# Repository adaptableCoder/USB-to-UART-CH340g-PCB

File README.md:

# USB to UART Converter (CH340G)

A compact **USB-to-UART adapter** based on the **CH340G**, implemented as a **USB-A edge connector board**.
Fabrication files have been generated; board fabrication is pending.

---

## Overview

This project implements a reliable USB-to-UART interface suitable for development, debugging, and embedded bring-up tasks.
Unlike typical breakout boards, this design uses a **USB-A edge connector**, allowing direct insertion into a host USB port without a cable.

The board supports both **5 V and 3.3 V UART logic levels** via jumper selection.

---

## Key Features

* CH340G USB-to-UART bridge
* USB-A **edge connector** (ENIG finish, bevelled)
* Jumper-selectable UART logic level (5 V / 3.3 V)
* On-board 3.3 V LDO
* USB ESD protection
* Polyfuse on VBUS for over-current protection
* Status LEDs (Power, TX, RX)
* RTS / CTS / DTR / DSR signals exposed
* 2-layer PCB, 1.6 mm thickness

---

## Design Tools Used

- KiCad (schematic capture, PCB layout, Gerber generation)

---

## Design Highlights

* **Grounding strategy**

  * Ground stitching vias near USB connector, ESD, and IC
  * Controlled return paths for high-speed signals

* **Clock integrity**

  * 12 MHz crystal placed close to XI/XO pins
  * Symmetric routing and tight loop area
  * Dedicated ground vias for crystal capacitors

* **Manufacturability**

  * ENIG finish selected for USB edge reliability
  * Bevelled edge specified for connector durability
  * Clean DRC-verified Gerber output

---

## Repository Structure

```
usb-to-uart-ch340g-pcb/
├── README.md
├── LICENSE
├── docs/
│   ├── images/
│   └── design-notes.md
├── schematic/
│   └── usb-to-uart-ch340g_schematic.pdf
├── pcb/
│   └── layout_screenshots/
├── fabrication/
│   ├── USB-to-UART-CH340G_Gerbers.zip
│   └── fab-notes.txt
├── datasheet/
│   └── CH340G_datasheet.pdf
└── KiCAD files/
    ├── usb-to-uart.kicad_pro
    ├── usb-to-uart.kicad_sch
    ├── usb-to-uart.kicad_prl
    └── usb-to-uart.kicad_pcb
```
---

## Fabrication Details

* Layers: 2
* Board thickness: 1.6 mm
* Copper weight: 1 oz
* Surface finish: ENIG
* USB edge connector: bevelled
* Solder mask: standard

---

## References and Attribution

* The USB-A edge connector footprint is **adapted from an open-source KiCad footprint library**. The original library is referenced here for attribution: https://github.com/vasya-zh/PCB-Edge-USB-connector-KiCad-library

* Component selection and implementation follow the **WCH CH340G datasheet** and standard USB Full-Speed design guidelines.

* Some YouTube tutorials and online articles on USB-to-UART designs were consulted during development.<br/>
[PCB Cupid](https://www.youtube.com/playlist?list=PLn6004q9oeqGl91KifK6xHGuqvXGb374G) <br/>
[Hardik Seth](https://www.youtube.com/@DIYwithHardik) <br/>
[Electronics Globe](https://www.youtube.com/@electronicsglobeofficial)

---

## License

This project is released under the **MIT License** unless stated otherwise.
Third-party references retain their respective licenses.

---

## Notes

This project was built as a **practical hardware design exercise**, with emphasis on finishing a complete, manufacturable PCB rather than producing a minimal demo board.
Future revisions may explore USB-C support or auto-voltage sensing.

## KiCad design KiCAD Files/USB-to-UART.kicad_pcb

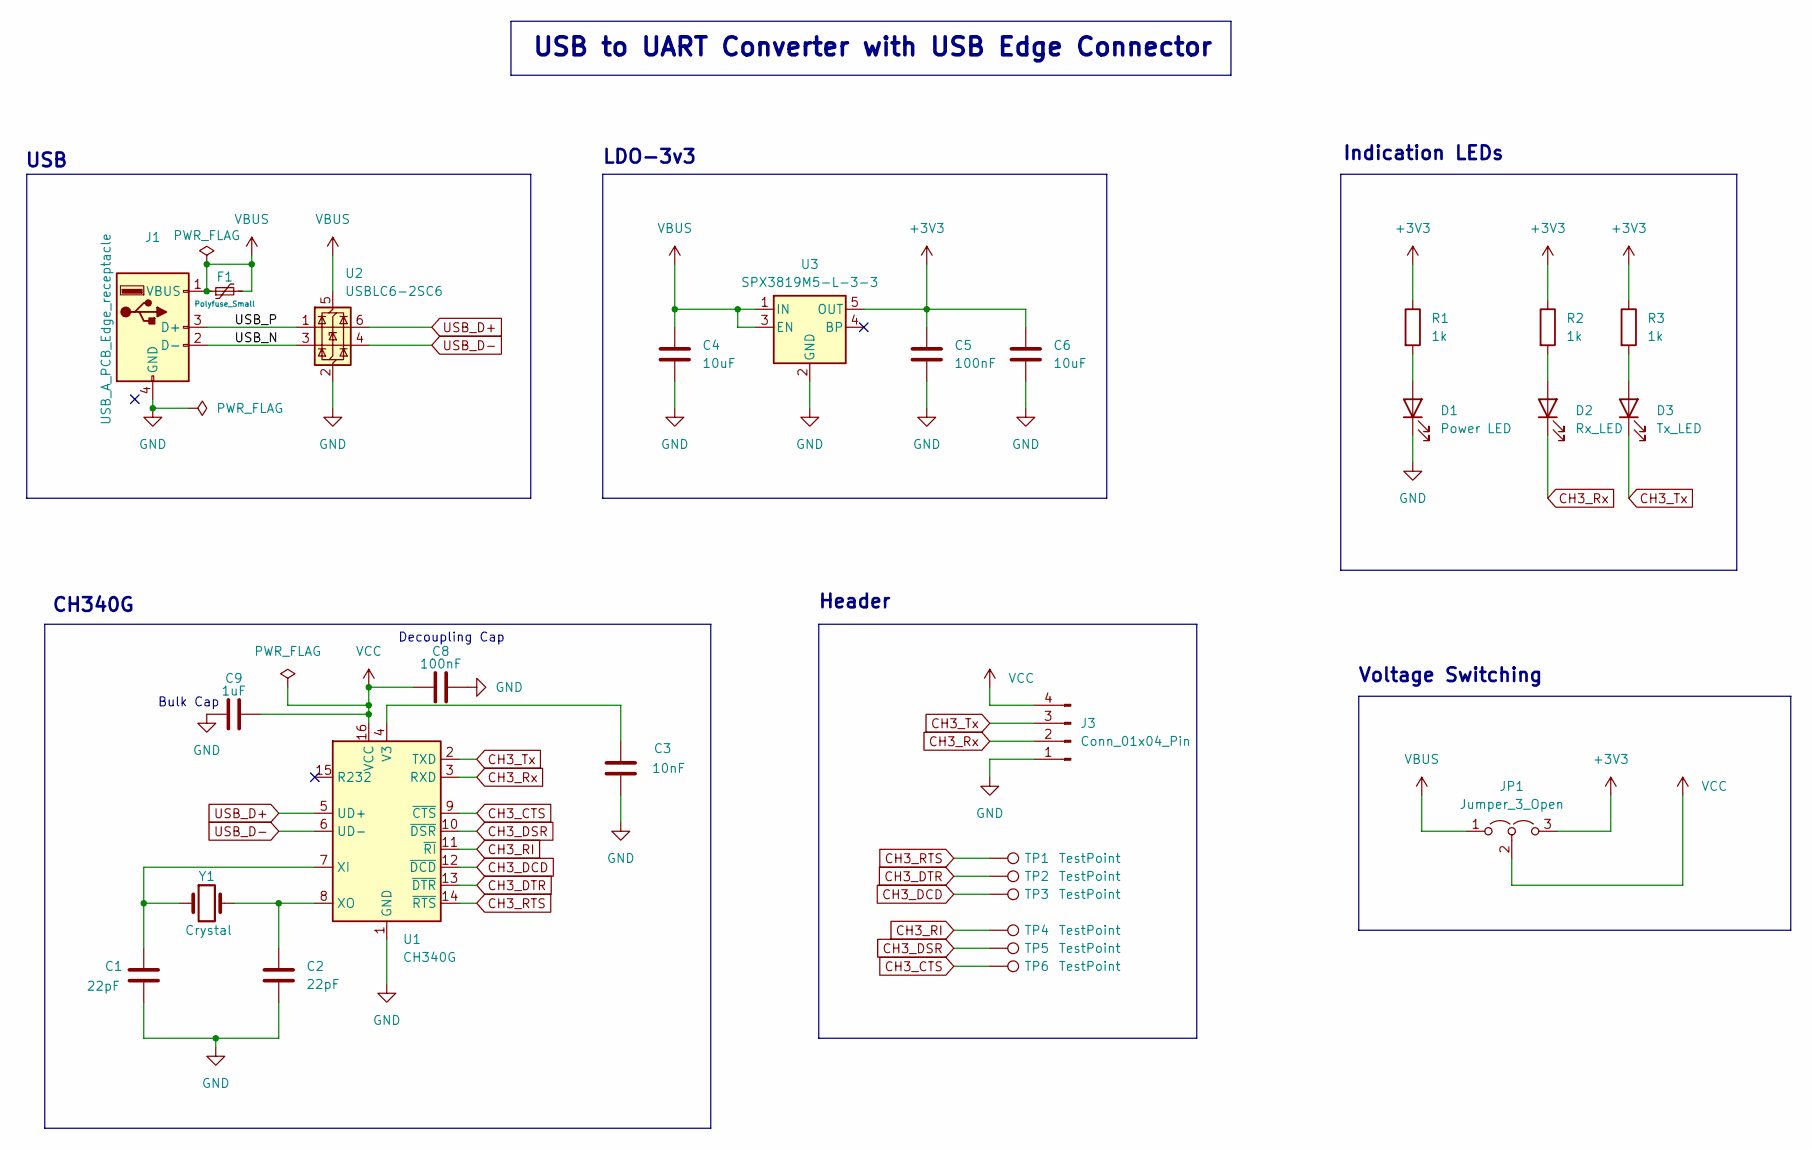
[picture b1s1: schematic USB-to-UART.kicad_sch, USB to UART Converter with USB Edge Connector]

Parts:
C1, C2: 22pF; C_0805_2012Metric_Pad1.18x1.45mm_HandSolder
C3: 10nF; C_0805_2012Metric_Pad1.18x1.45mm_HandSolder
C4, C6: 10uF; C_0805_2012Metric_Pad1.18x1.45mm_HandSolder
C5, C8: 100nF; C_0805_2012Metric_Pad1.18x1.45mm_HandSolder
C9: 1uF; C_0805_2012Metric_Pad1.18x1.45mm_HandSolder
D1: Power LED; LED_0805_2012Metric_Pad1.15x1.40mm_HandSolder
D2: Rx_LED; LED_0805_2012Metric_Pad1.15x1.40mm_HandSolder
D3: Tx_LED; LED_0805_2012Metric_Pad1.15x1.40mm_HandSolder
F1: Polyfuse_Small; Fuse_1206_3216Metric_Pad1.42x1.75mm_HandSolder
J1: USB_A_PCB_Edge_receptacle
J3: Conn_01x04_Pin; PinHeader_1x04_P2.54mm_Horizontal
JP1: Jumper_3_Open; PinHeader_1x03_P2.54mm_Vertical
R1, R2, R3: 1k; R_0805_2012Metric_Pad1.20x1.40mm_HandSolder
TP1, TP2, TP3, TP4, TP5, TP6: TestPoint; TestPoint_Pad_D1.0mm
U1: CH340G; SOIC-16_3.9x9.9mm_P1.27mm
U2: USBLC6-2SC6; SOT-23-6
U3: SPX3819M5-L-3-3; SOT-23-5
Y1: Crystal; Crystal_HC49-U_Vertical

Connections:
+3V3: C5.1, C6.1, JP1.3 (B), R1.1, R2.1, R3.1, U3.5 (OUT)
/USB_N: J1.2 (D-), U2.3 (I/O2)
/USB_P: J1.3 (D+), U2.1 (I/O1)
CH3_CTS: TP6.1, U1.9 (~CTS)
CH3_DCD: TP3.1, U1.12 (~DCD)
CH3_DSR: TP5.1, U1.10 (~DSR)
CH3_DTR: TP2.1, U1.13 (~DTR)
CH3_RI: TP4.1, U1.11 (~RI)
CH3_RTS: TP1.1, U1.14 (~RTS)
CH3_Rx: D2.1 (K), J3.2, U1.3 (RXD)
CH3_Tx: D3.1 (K), J3.3, U1.2 (TXD)
GND: C1.2, C2.2, C3.2, C4.2, C5.2, C6.2, C8.2, C9.1, D1.1 (K), J1.4 (GND), J3.1, U1.1 (GND), U2.2 (GND), U3.2 (GND)
unnamed: D1.2 (A), R1.2
unnamed: D2.2 (A), R2.2
unnamed: D3.2 (A), R3.2
unnamed: C3.1, U1.4 (V3)
unnamed: C1.1, U1.7 (XI), Y1.1
unnamed: C2.1, U1.8 (XO), Y1.2
USB_D+: U1.5 (UD+), U2.6 (I/O1)
USB_D-: U1.6 (UD-), U2.4 (I/O2)
VBUS: C4.1, F1.1, F1.2, J1.1 (VBUS), JP1.1 (A), U2.5 (VBUS), U3.1 (IN), U3.3 (EN)
VCC: C8.1, C9.2, J3.4, JP1.2 (C), U1.16 (VCC)

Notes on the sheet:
CH340G
Decoupling Cap
Header
USB
Voltage Switching
USB to UART Converter with USB Edge Connector
Bulk Cap
LDO-3v3
Indication LEDs

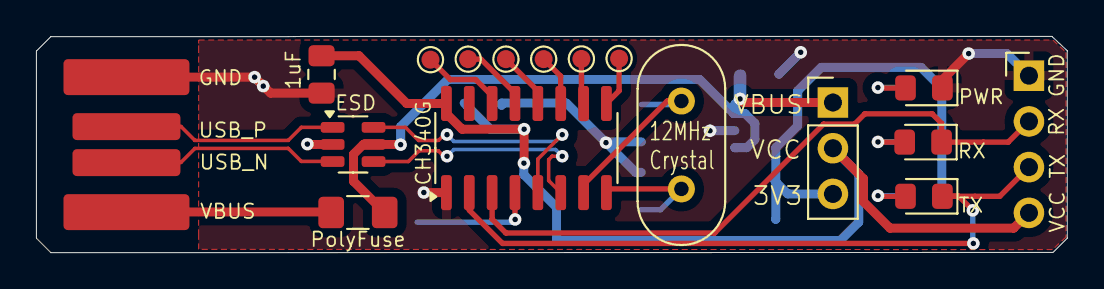
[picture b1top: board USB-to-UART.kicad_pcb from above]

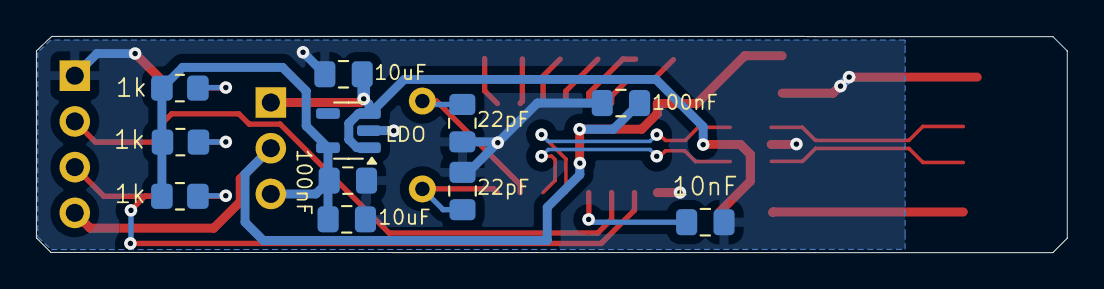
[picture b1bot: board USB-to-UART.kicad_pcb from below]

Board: 2 copper layers, 57.3 x 12.0 mm, 28 parts (11 on the bottom side), 22 nets.

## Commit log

2026-01-26 readme updated
2026-02-14 Readme updated with PCB 3D Pics
2026-02-27 Updated README.md for KiCAD files
